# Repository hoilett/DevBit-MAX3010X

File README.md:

# DevBit-MAX3010X
DevBit for the MAX3010x Pulse Oximeter and Heart Rate Sensor ICs

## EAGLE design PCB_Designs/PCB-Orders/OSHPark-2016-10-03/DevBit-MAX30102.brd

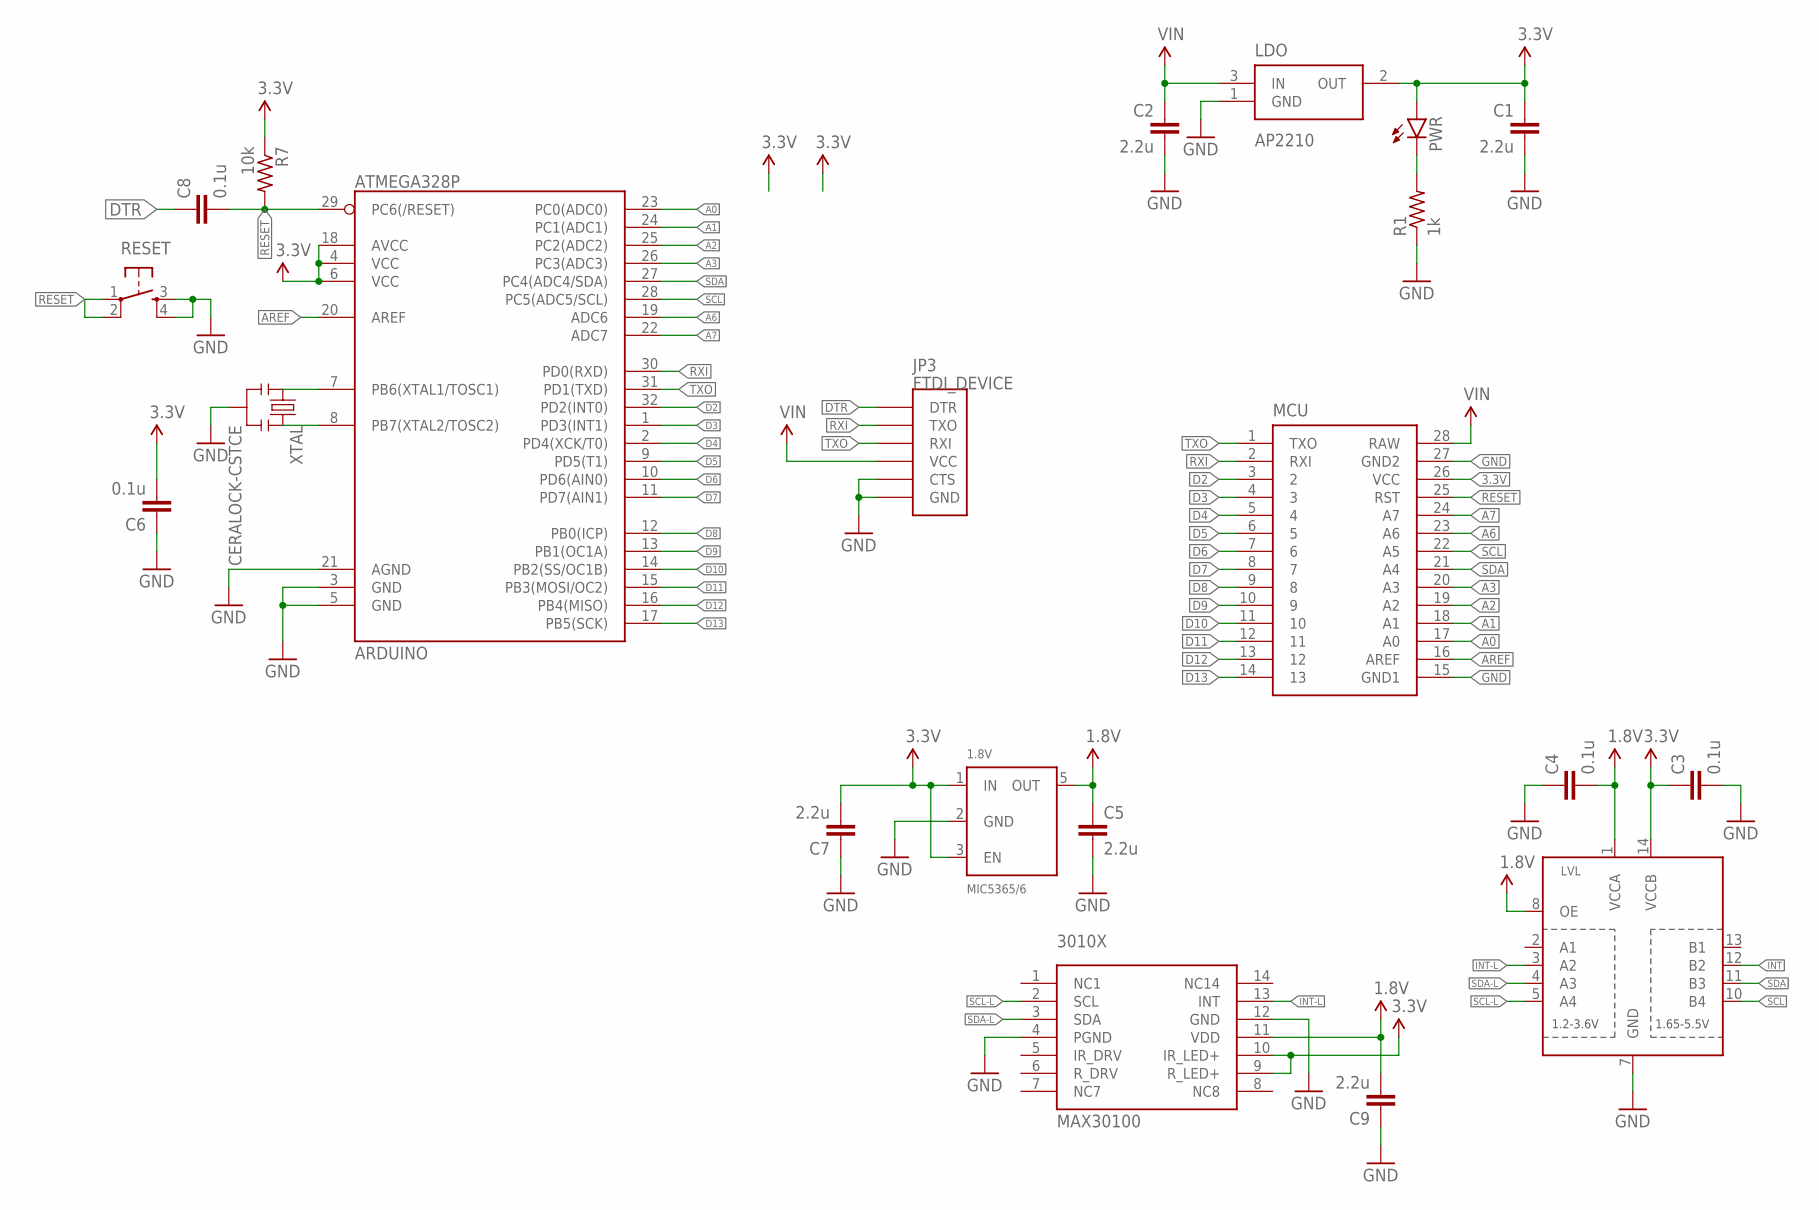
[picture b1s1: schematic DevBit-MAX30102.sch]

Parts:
1.8V: MIC5365/6; SC-70-5
3010X: MAX30100; OESIP14
ARDUINO: ATMEGA328P; TQFP32-08
C1, C2, C5, C7, C9: 2.2u; C0402
C3, C4, C6, C8: 0.1u; C0402
JP3: FTDI_DEVICE
LDO: AP2210; SOT23
LVL: TXB0104PWR; TSSOP14
MCU: DEVBASIC-V1; DEVBIT-BASIC-V1
PWR: LED0603; LED-0603
R1: 1k; R0402
R7: 10k; R0402
RESET: BUTTON-PTS830GG140; BUTTON-GULLWING
XTAL: CERALOCK-CSTCE; RESONATOR-00

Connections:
1.8V: 1.8V.5 (OUT), 3010X.11 (VDD), C4.2, C5.1, C9.2, LVL.1 (VCCA), LVL.8 (OE)
3.3V: 1.8V.1 (IN), 1.8V.3 (EN), 3010X.9 (R_LED+), 3010X.10 (IR_LED+), ARDUINO.4 (VCC), ARDUINO.6 (VCC), ARDUINO.18 (AVCC), C1.1, C3.1, C6.2, C7.2, LDO.2 (OUT), LVL.14 (VCCB), MCU.26 (VCC), PWR.A, R7.1
A0: ARDUINO.23 (PC0(ADC0)), MCU.17 (A0)
A1: ARDUINO.24 (PC1(ADC1)), MCU.18 (A1)
A2: ARDUINO.25 (PC2(ADC2)), MCU.19 (A2)
A3: ARDUINO.26 (PC3(ADC3)), MCU.20 (A3)
A6: ARDUINO.19 (ADC6), MCU.23 (A6)
A7: ARDUINO.22 (ADC7), MCU.24 (A7)
AREF: ARDUINO.20 (AREF), MCU.16 (AREF)
D2: ARDUINO.32 (PD2(INT0)), MCU.3 (2)
D3: ARDUINO.1 (PD3(INT1)), MCU.4 (3)
D4: ARDUINO.2 (PD4(XCK/T0)), MCU.5 (4)
D5: ARDUINO.9 (PD5(T1)), MCU.6 (5)
D6: ARDUINO.10 (PD6(AIN0)), MCU.7 (6)
D7: ARDUINO.11 (PD7(AIN1)), MCU.8 (7)
D8: ARDUINO.12 (PB0(ICP)), MCU.9 (8)
D9: ARDUINO.13 (PB1(OC1A)), MCU.10 (9)
D10: ARDUINO.14 (PB2(SS/OC1B)), MCU.11 (10)
D11: ARDUINO.15 (PB3(MOSI/OC2)), MCU.12 (11)
D12: ARDUINO.16 (PB4(MISO)), MCU.13 (12)
D13: ARDUINO.17 (PB5(SCK)), MCU.14 (13)
DTR: C8.1, JP3.DTR
GND: 1.8V.2 (GND), 3010X.4 (PGND), 3010X.12 (GND), ARDUINO.3 (GND), ARDUINO.5 (GND), ARDUINO.21 (AGND), C1.2, C2.2, C3.2, C4.1, C5.2, C6.1, C7.1, C9.1, JP3.CTS, JP3.GND, LDO.1 (GND), LVL.7 (GND), MCU.15 (GND1), MCU.27 (GND2), R1.1, RESET.3, RESET.4, XTAL.2
INT: LVL.12 (B2)
INT-L: 3010X.13 (INT), LVL.3 (A2)
unnamed: ARDUINO.7 (PB6(XTAL1/TOSC1)), XTAL.1
unnamed: ARDUINO.8 (PB7(XTAL2/TOSC2)), XTAL.3
unnamed: PWR.C, R1.2
RESET: ARDUINO.29 (PC6(/RESET)), C8.2, MCU.25 (RST), R7.2, RESET.1, RESET.2
RXI: ARDUINO.30 (PD0(RXD)), JP3.TXO, MCU.2 (RXI)
SCL: ARDUINO.28 (PC5(ADC5/SCL)), LVL.10 (B4), MCU.22 (A5)
SCL-L: 3010X.2 (SCL), LVL.5 (A4)
SDA: ARDUINO.27 (PC4(ADC4/SDA)), LVL.11 (B3), MCU.21 (A4)
SDA-L: 3010X.3 (SDA), LVL.4 (A3)
TXO: ARDUINO.31 (PD1(TXD)), JP3.RXI, MCU.1 (TXO)
VIN: C2.1, JP3.VCC, LDO.3 (IN), MCU.28 (RAW)

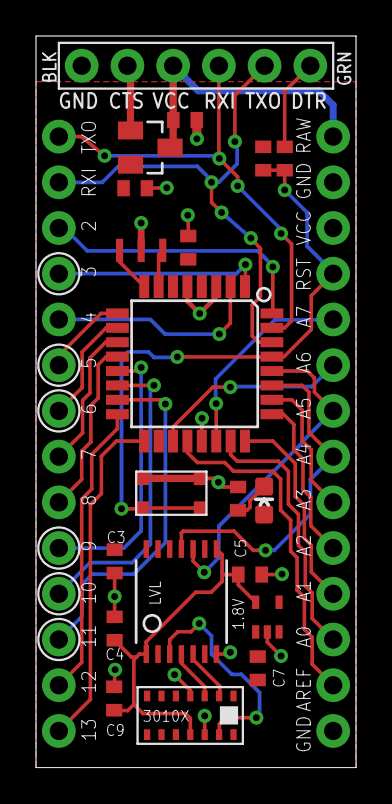
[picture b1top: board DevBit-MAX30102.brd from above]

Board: 2 copper layers, 17.8 x 40.6 mm, 21 parts (0 on the bottom side), 35 nets.

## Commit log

2016-10-03 Create LICENSE-hardware
2016-10-03 first PCB design files and OSH Park order

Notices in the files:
PCB_Designs/DevBit-MAX30102.sch:
Creative Commons License
parts and their libraries:
SparkFun-DigitalIC: Licensing: Creative Commons ShareAlike 4.0 International - https://creativecommons.org/licenses/by-sa/4.0
